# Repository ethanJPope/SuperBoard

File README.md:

# Superboard
An awesome devboard that can easily streamline any simple hardware project. With a custom RP2040 setup featuring USB-C and two dual motor controllers, so you can run up to four motors off of this single board.

## Images

## Price breakdown

PCB Components $18.20
PCB $5.12
Motor controllers- $3.06

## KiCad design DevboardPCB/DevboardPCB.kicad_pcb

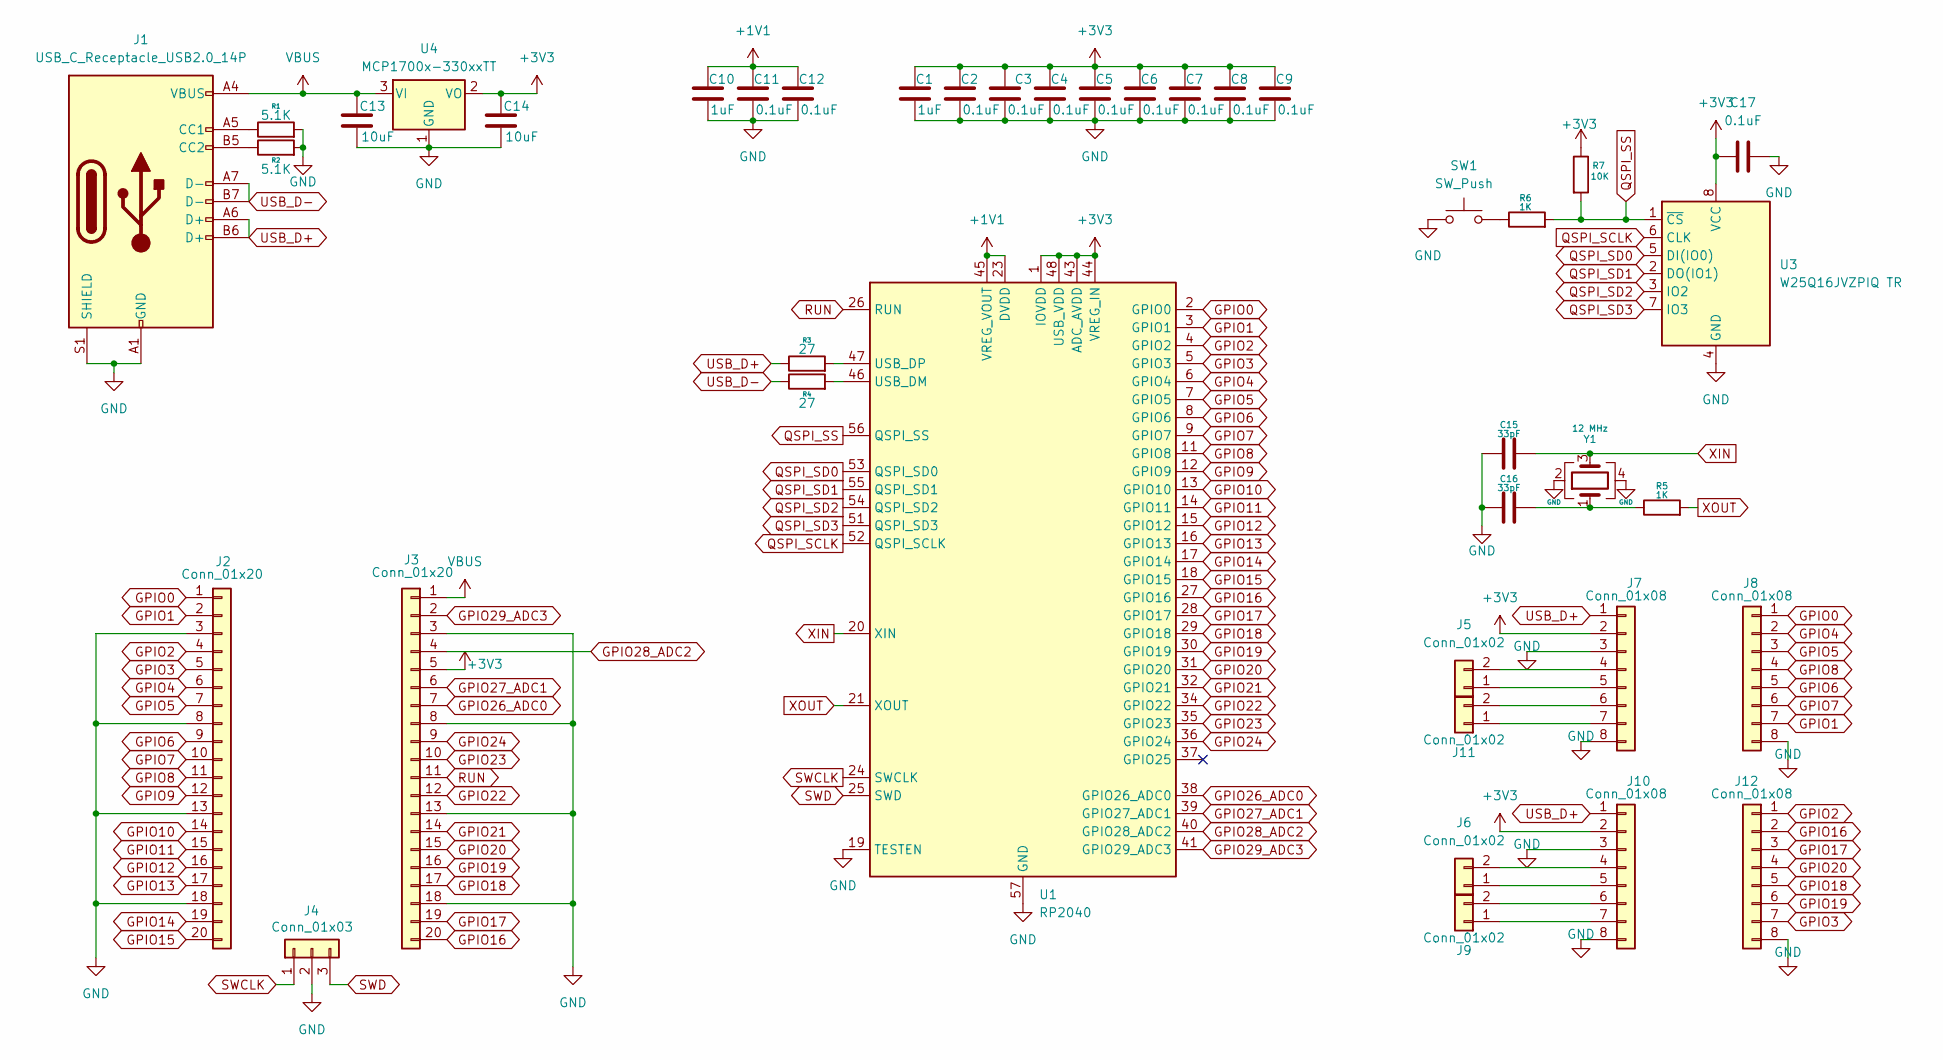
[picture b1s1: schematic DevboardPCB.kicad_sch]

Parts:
C1, C10: 1uF; C_0402_1005Metric
C2, C3, C4, C5, C6, C7, C8, C9, C11, C12, C17: 0.1uF; C_0402_1005Metric
C13, C14: 10uF; C_0603_1608Metric
C15, C16: 33pF; C_0402_1005Metric
J1: USB_C_Receptacle_USB2.0_14P; USB_C_Receptacle_HRO_TYPE-C-31-M-12
J2, J3: Conn_01x20; PinHeader_1x20_P2.54mm_Vertical
J4: Conn_01x03; PinHeader_1x03_P2.54mm_Vertical
J5, J6, J9, J11: Conn_01x02; PinHeader_1x02_P2.54mm_Vertical
J7, J8, J10, J12: Conn_01x08; PinHeader_1x08_P2.54mm_Vertical
R1, R2: 5.1K; R_0402_1005Metric
R3, R4: 27; R_0402_1005Metric
R5, R6: 1K; R_0402_1005Metric
R7: 10K; R_0402_1005Metric
SW1: SW_Push; SW_Push_SPST_NO_Alps_SKRK
U1: RP2040; QFN-56-1EP_7x7mm_P0.4mm_EP3.2x3.2mm
U3: W25Q16JVZPIQ TR; Winbond_USON-8-1EP_3x2mm_P0.5mm_EP0.2x1.6mm
U4: MCP1700x-330xxTT; SOT-23
Y1: 12 MHz; Crystal_SMD_3225-4Pin_3.2x2.5mm

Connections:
+1V1: C10.1, C11.1, C12.1, U1.23 (DVDD), U1.45 (VREG_VOUT), U1.50 (DVDD)
+3V3: C1.1, C2.1, C3.1, C4.1, C5.1, C6.1, C7.1, C8.1, C9.1, C14.1, C17.1, J3.5, J7.2, J10.2, R7.1, U1.1 (IOVDD), U1.10 (IOVDD), U1.22 (IOVDD), U1.33 (IOVDD), U1.42 (IOVDD), U1.43 (ADC_AVDD), U1.44 (VREG_IN), U1.48 (USB_VDD), U1.49 (IOVDD), U3.8 (VCC), U4.2 (VO)
GND: C1.2, C2.2, C3.2, C4.2, C5.2, C6.2, C7.2, C8.2, C9.2, C10.2, C11.2, C12.2, C13.2, C14.2, C15.1, C16.1, C17.2, J1.A1 (GND), J1.A12 (GND), J1.B1 (GND), J1.B12 (GND), J1.S1 (SHIELD), J2.3, J2.8, J2.13, J2.18, J3.3, J3.8, J3.13, J3.18, J4.2, J7.3, J7.8, J8.8, J10.3, J10.8, J12.8, R1.2, R2.2, SW1.1, U1.19 (TESTEN), U1.57 (GND), U3.4 (GND), U4.1 (GND), Y1.2, Y1.4
GPIO0: J2.1, J8.1, U1.2 (GPIO0)
GPIO1: J2.2, J8.7, U1.3 (GPIO1)
GPIO2: J2.4, J12.1, U1.4 (GPIO2)
GPIO3: J2.5, J12.7, U1.5 (GPIO3)
GPIO4: J2.6, J8.2, U1.6 (GPIO4)
GPIO5: J2.7, J8.3, U1.7 (GPIO5)
GPIO6: J2.9, J8.5, U1.8 (GPIO6)
GPIO7: J2.10, J8.6, U1.9 (GPIO7)
GPIO8: J2.11, J8.4, U1.11 (GPIO8)
GPIO9: J2.12, U1.12 (GPIO9)
GPIO10: J2.14, U1.13 (GPIO10)
GPIO11: J2.15, U1.14 (GPIO11)
GPIO12: J2.16, U1.15 (GPIO12)
GPIO13: J2.17, U1.16 (GPIO13)
GPIO14: J2.19, U1.17 (GPIO14)
GPIO15: J2.20, U1.18 (GPIO15)
GPIO16: J3.20, J12.2, U1.27 (GPIO16)
GPIO17: J3.19, J12.3, U1.28 (GPIO17)
GPIO18: J3.17, J12.5, U1.29 (GPIO18)
GPIO19: J3.16, J12.6, U1.30 (GPIO19)
GPIO20: J3.15, J12.4, U1.31 (GPIO20)
GPIO21: J3.14, U1.32 (GPIO21)
GPIO22: J3.12, U1.34 (GPIO22)
GPIO23: J3.10, U1.35 (GPIO23)
GPIO24: J3.9, U1.36 (GPIO24)
GPIO26_ADC0: J3.7, U1.38 (GPIO26_ADC0)
GPIO27_ADC1: J3.6, U1.39 (GPIO27_ADC1)
GPIO28_ADC2: J3.4, U1.40 (GPIO28_ADC2)
GPIO29_ADC3: J3.2, U1.41 (GPIO29_ADC3)
unnamed: C16.2, R5.1, Y1.1
unnamed: J1.A5 (CC1), R1.1
unnamed: J1.B5 (CC2), R2.1
unnamed: J5.1, J7.5
unnamed: J5.2, J7.4
unnamed: J6.2, J10.4
unnamed: J6.1, J10.5
unnamed: J9.2, J10.6
unnamed: J9.1, J10.7
unnamed: J7.7, J11.1
unnamed: J7.6, J11.2
unnamed: R6.1, SW1.2
unnamed: R4.2, U1.46 (USB_DM)
unnamed: R3.2, U1.47 (USB_DP)
QSPI_SCLK: U1.52 (QSPI_SCLK), U3.6 (CLK)
QSPI_SD0: U1.53 (QSPI_SD0), U3.5 (DI(IO0))
QSPI_SD1: U1.55 (QSPI_SD1), U3.2 (DO(IO1))
QSPI_SD2: U1.54 (QSPI_SD2), U3.3 (IO2)
QSPI_SD3: U1.51 (QSPI_SD3), U3.7 (IO3)
QSPI_SS: R6.2, R7.2, U1.56 (QSPI_SS), U3.1 (~CS)
RUN: J3.11, U1.26 (RUN)
SWCLK: J4.1, U1.24 (SWCLK)
SWD: J4.3, U1.25 (SWD)
USB_D+: J1.A6 (D+), J1.B6 (D+), J7.1, J10.1, R3.1
USB_D-: J1.A7 (D-), J1.B7 (D-), R4.1
VBUS: C13.1, J1.A4 (VBUS), J1.A9 (VBUS), J1.B4 (VBUS), J1.B9 (VBUS), J3.1, U4.3 (VI)
XIN: C15.2, U1.20 (XIN), Y1.3
XOUT: R5.2, U1.21 (XOUT)

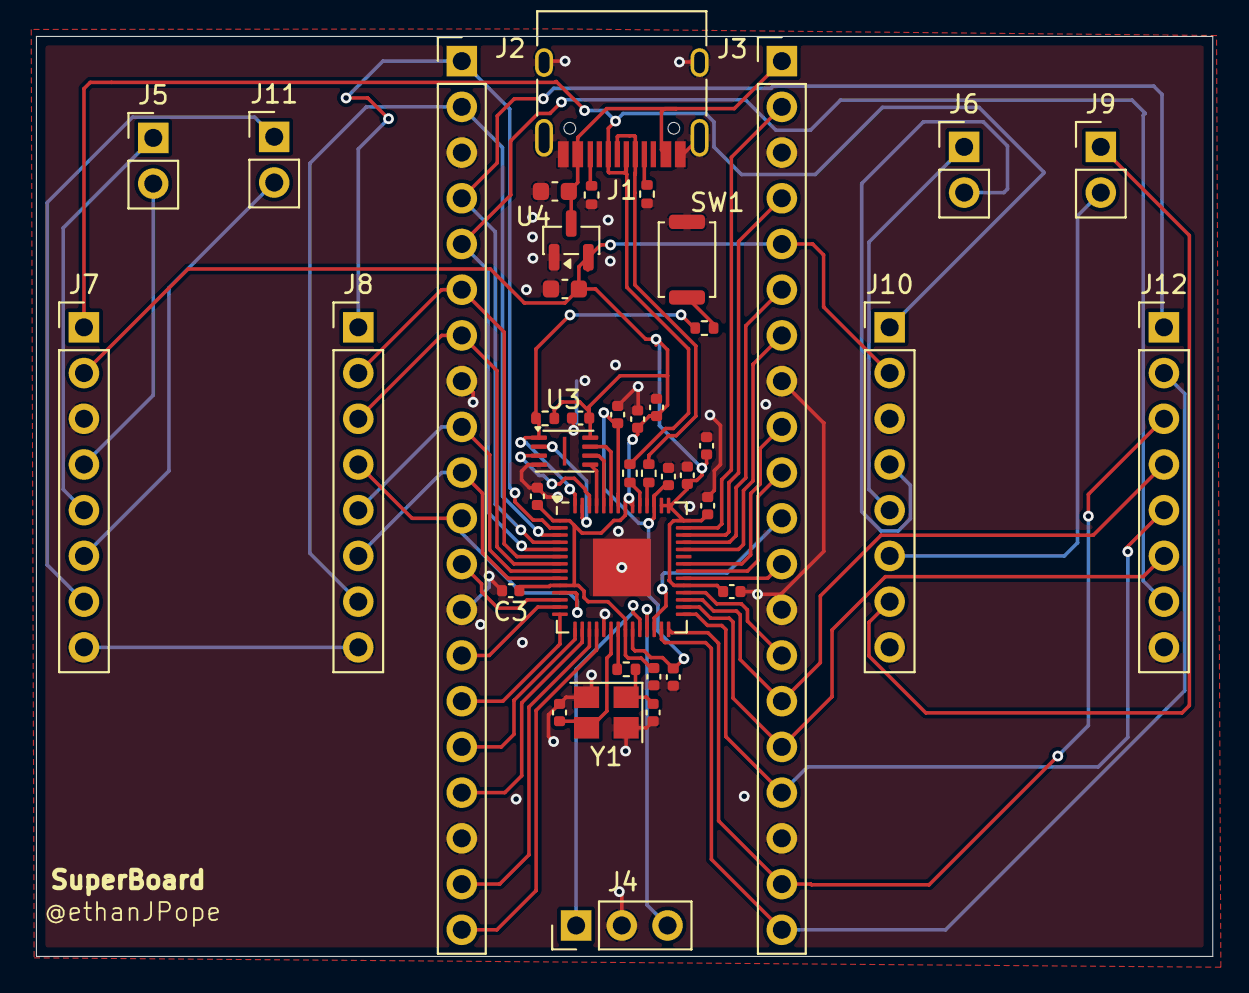
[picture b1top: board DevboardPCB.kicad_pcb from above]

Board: 2 copper layers, 65.3 x 51.1 mm, 41 parts (0 on the bottom side), 60 nets.

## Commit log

2025-11-27 Created my schematic
2025-12-02 finished routing
2025-12-02 Initialize README with project details and images
    Added project description, images, and price breakdown.
